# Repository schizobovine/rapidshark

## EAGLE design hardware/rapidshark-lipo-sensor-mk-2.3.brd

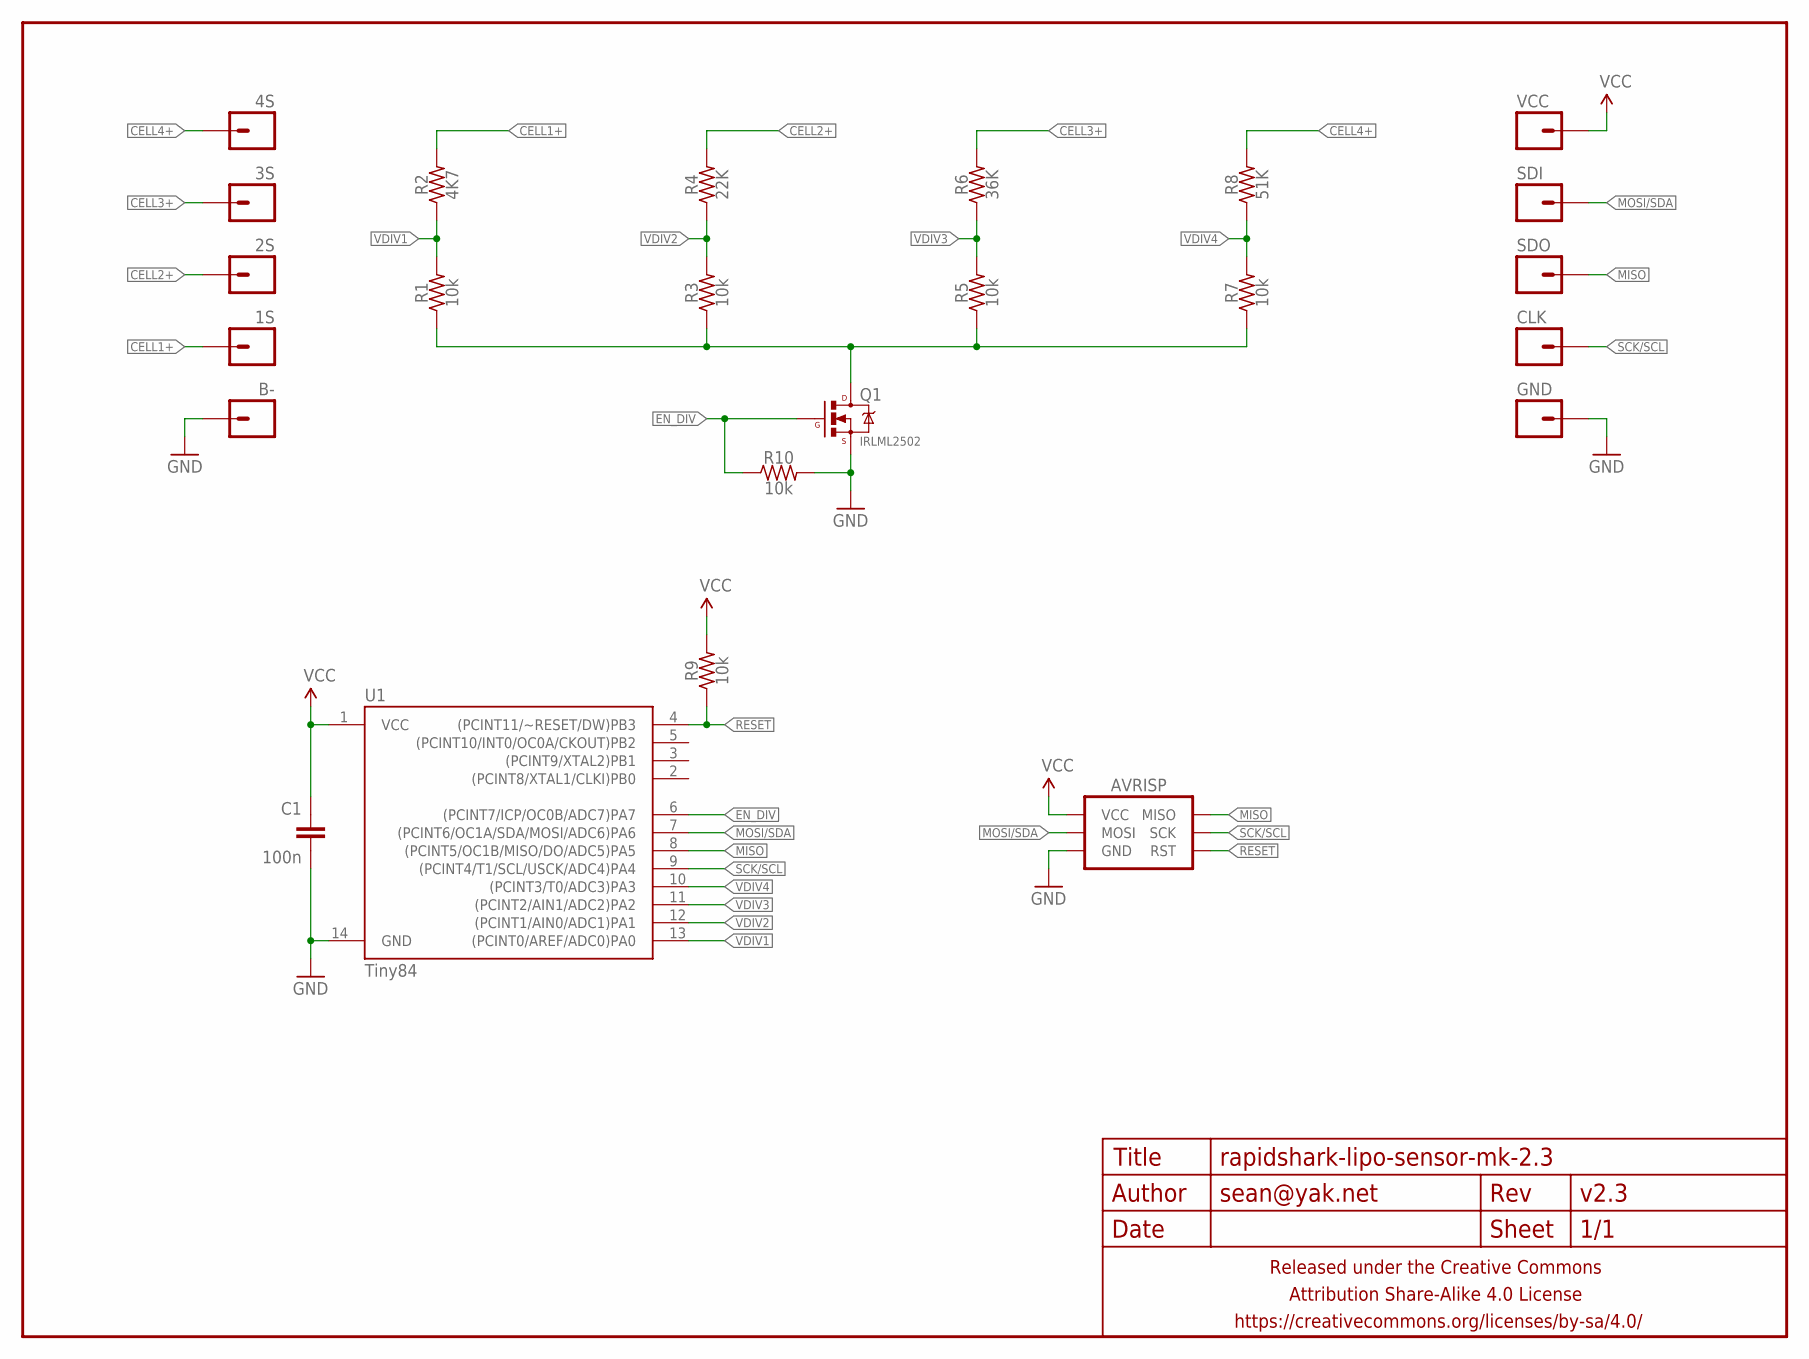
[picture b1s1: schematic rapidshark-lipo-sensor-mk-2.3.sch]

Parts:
1S, 2S, 3S, 4S: M01PTH-0.9MM; 1X01-0.9MM
AVRISP: AVR_SPI_PRG_6TESTPOINTS; 2X3_TEST_POINTS
B-: M01PTH-0.9MM; 1X01-0.9MM
C1: 100n; C0603-TIGHTER
CLK: M01PTH-0.9MM; 1X01-0.9MM
FRAME1: FRAME-LETTERNO_PACKAGE; DUMMY
GND: M01PTH-0.9MM; 1X01-0.9MM
Q1: IRLML2502; SOT23
R1, R3, R5, R7, R9, R10: 10k; R0603-TIGHTER
R2: 4K7; R0603-TIGHTER
R4: 22K; R0603-TIGHTER
R6: 36K; R0603-TIGHTER
R8: 51K; R0603-TIGHTER
SDI: M01PTH-0.9MM; 1X01-0.9MM
SDO: M01PTH-0.9MM; 1X01-0.9MM
U1: Tiny84; SO14
VCC: M01PTH-0.9MM; 1X01-0.9MM

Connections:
CELL1+: 1S.1, R2.2
CELL2+: 2S.1, R4.2
CELL3+: 3S.1, R6.2
CELL4+: 4S.1, R8.2
EN_DIV: Q1.1 (G), R10.1, U1.6 ((PCINT7/ICP/OC0B/ADC7)PA7)
GND: AVRISP.6 (GND), B-.1, C1.2, GND.1, Q1.2 (S), R10.2, U1.14 (GND)
MISO: AVRISP.1 (MISO), SDO.1, U1.8 ((PCINT5/OC1B/MISO/DO/ADC5)PA5)
MOSI/SDA: AVRISP.4 (MOSI), SDI.1, U1.7 ((PCINT6/OC1A/SDA/MOSI/ADC6)PA6)
unnamed: Q1.3 (D), R1.1, R3.1, R5.1, R7.1
RESET: AVRISP.5 (RST), R9.1, U1.4 ((PCINT11/~RESET/DW)PB3)
SCK/SCL: AVRISP.3 (SCK), CLK.1, U1.9 ((PCINT4/T1/SCL/USCK/ADC4)PA4)
VCC: AVRISP.2 (VCC), C1.1, R9.2, U1.1 (VCC), VCC.1
VDIV1: R1.2, R2.1, U1.13 ((PCINT0/AREF/ADC0)PA0)
VDIV2: R3.2, R4.1, U1.12 ((PCINT1/AIN0/ADC1)PA1)
VDIV3: R5.2, R6.1, U1.11 ((PCINT2/AIN1/ADC2)PA2)
VDIV4: R7.2, R8.1, U1.10 ((PCINT3/T0/ADC3)PA3)

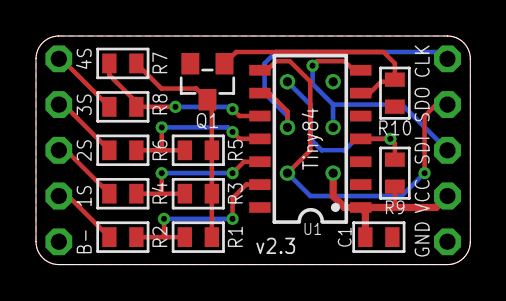
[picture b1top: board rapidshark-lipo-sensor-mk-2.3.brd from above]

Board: 2 copper layers, 24.1 x 12.7 mm, 25 parts (1 on the bottom side), 16 nets.

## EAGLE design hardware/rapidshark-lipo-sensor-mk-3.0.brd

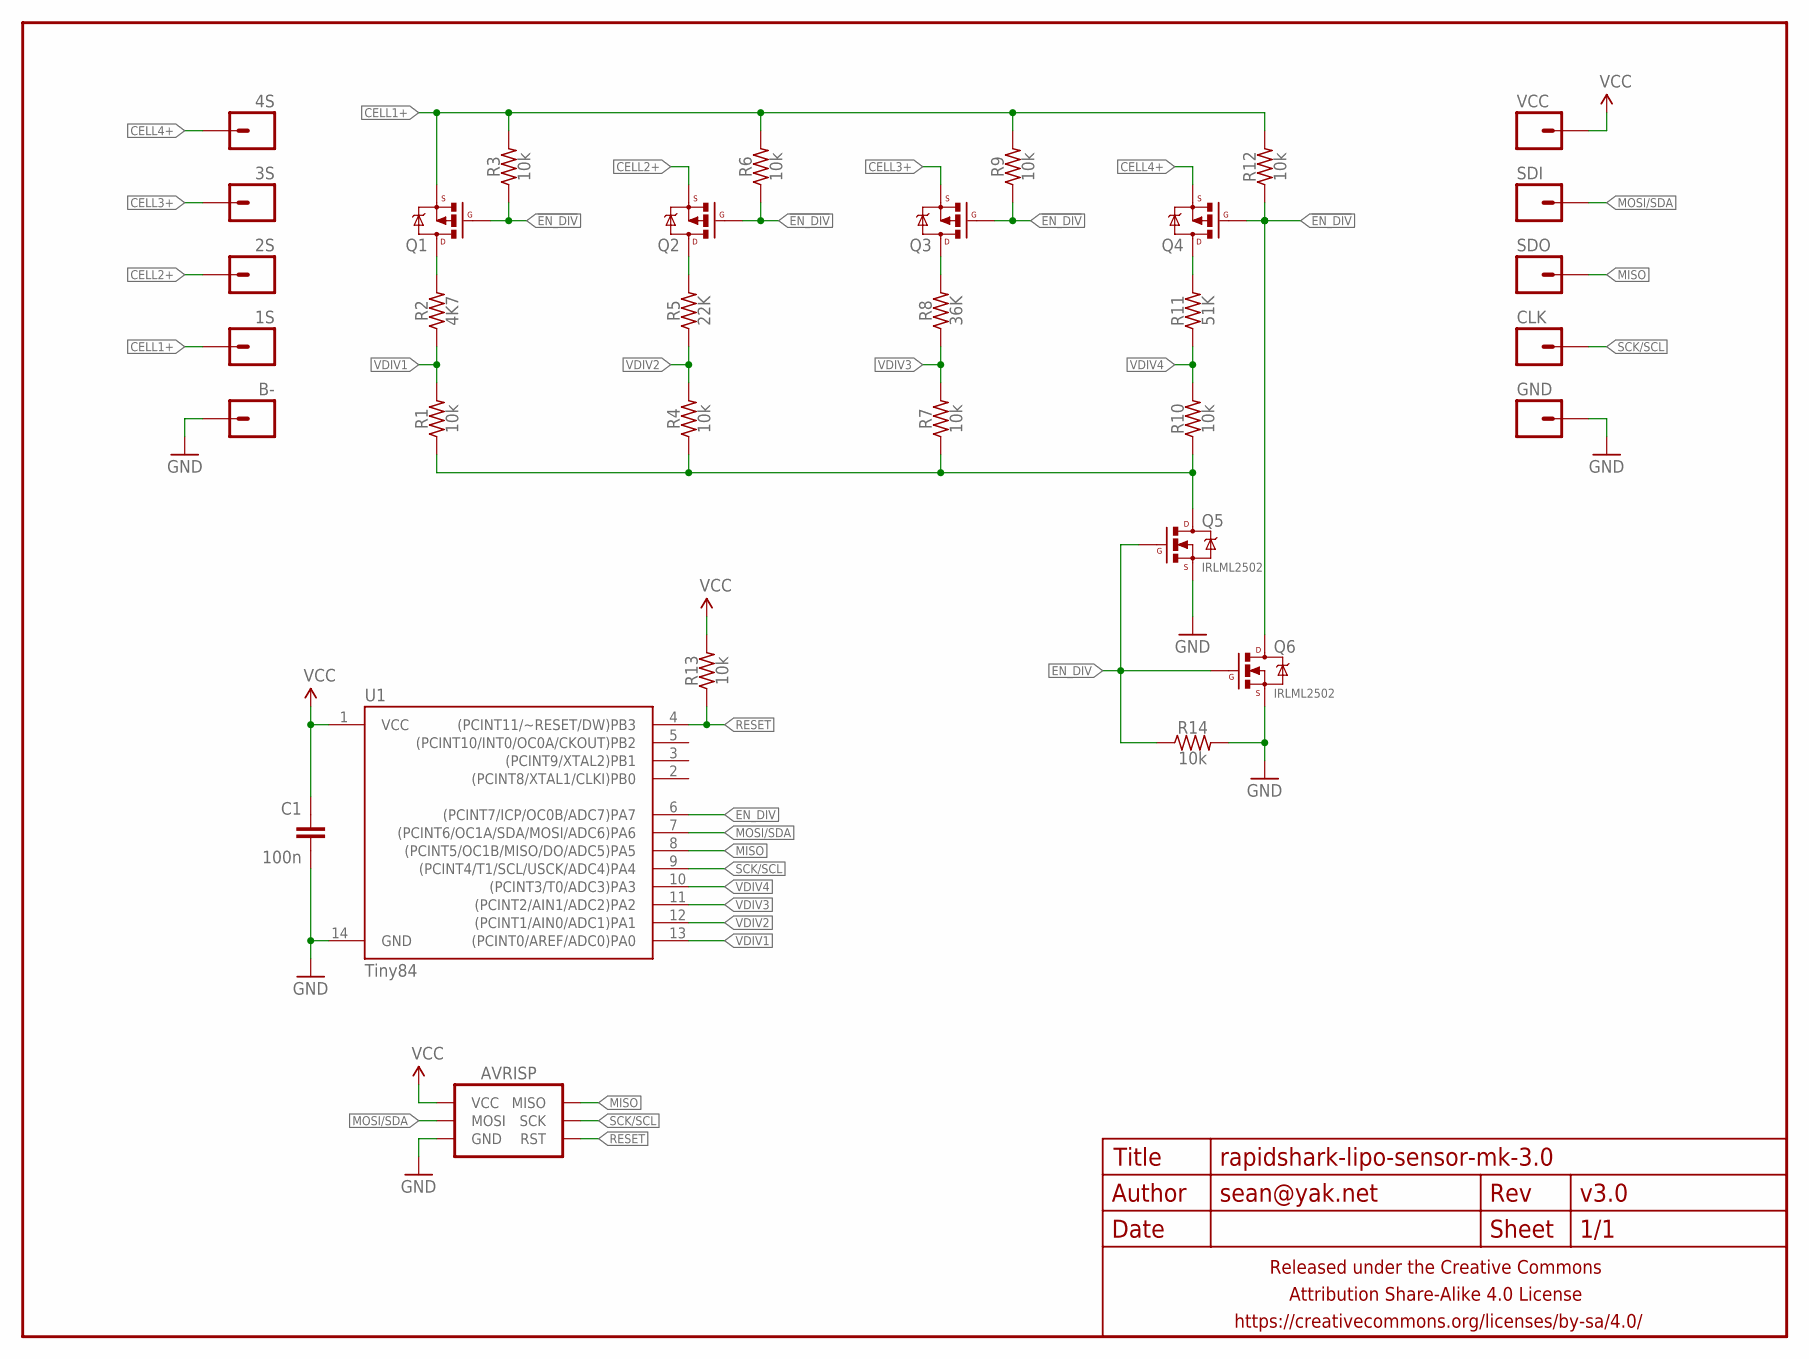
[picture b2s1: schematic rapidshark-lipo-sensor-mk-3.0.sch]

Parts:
1S, 2S, 3S, 4S: M01PTH-0.9MM; 1X01-0.9MM
AVRISP: AVR_SPI_PRG_6SMD_TEST_POINTS; 2X3_SMD_TEST_POINTS
B-: M01PTH-0.9MM; 1X01-0.9MM
C1: 100n; C0603-TIGHTER
CLK: M01PTH-0.9MM; 1X01-0.9MM
FRAME1: FRAME-LETTERNO_PACKAGE; DUMMY
GND: M01PTH-0.9MM; 1X01-0.9MM
Q1, Q2, Q3, Q4: MOSFET-PCHANNELSOT-23; SOT23
Q5, Q6: IRLML2502; SOT23
R1, R3, R4, R6, R7, R9, R10, R12, R13, R14: 10k; R0603-TIGHTER
R2: 4K7; R0603-TIGHTER
R5: 22K; R0603-TIGHTER
R8: 36K; R0603-TIGHTER
R11: 51K; R0603-TIGHTER
SDI: M01PTH-0.9MM; 1X01-0.9MM
SDO: M01PTH-0.9MM; 1X01-0.9MM
U1: Tiny84; SO14
VCC: M01PTH-0.9MM; 1X01-0.9MM

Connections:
!EN_DIV: Q1.1 (G), Q2.1 (G), Q3.1 (G), Q4.1 (G), Q6.3 (D), R3.1, R6.1, R9.1, R12.1
CELL1+: 1S.1, Q1.2 (S), R3.2, R6.2, R9.2, R12.2
CELL2+: 2S.1, Q2.2 (S)
CELL3+: 3S.1, Q3.2 (S)
CELL4+: 4S.1, Q4.2 (S)
EN_DIV: Q5.1 (G), Q6.1 (G), R14.1, U1.6 ((PCINT7/ICP/OC0B/ADC7)PA7)
GND: AVRISP.6 (GND), B-.1, C1.2, GND.1, Q5.2 (S), Q6.2 (S), R14.2, U1.14 (GND)
MISO: AVRISP.1 (MISO), SDO.1, U1.8 ((PCINT5/OC1B/MISO/DO/ADC5)PA5)
MOSI/SDA: AVRISP.4 (MOSI), SDI.1, U1.7 ((PCINT6/OC1A/SDA/MOSI/ADC6)PA6)
unnamed: Q5.3 (D), R1.1, R4.1, R7.1, R10.1
unnamed: Q2.3 (D), R5.2
unnamed: Q3.3 (D), R8.2
unnamed: Q4.3 (D), R11.2
unnamed: Q1.3 (D), R2.2
RESET: AVRISP.5 (RST), R13.1, U1.4 ((PCINT11/~RESET/DW)PB3)
SCK/SCL: AVRISP.3 (SCK), CLK.1, U1.9 ((PCINT4/T1/SCL/USCK/ADC4)PA4)
VCC: AVRISP.2 (VCC), C1.1, R13.2, U1.1 (VCC), VCC.1
VDIV1: R1.2, R2.1, U1.13 ((PCINT0/AREF/ADC0)PA0)
VDIV2: R4.2, R5.1, U1.12 ((PCINT1/AIN0/ADC1)PA1)
VDIV3: R7.2, R8.1, U1.11 ((PCINT2/AIN1/ADC2)PA2)
VDIV4: R10.2, R11.1, U1.10 ((PCINT3/T0/ADC3)PA3)

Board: 2 copper layers, 34 parts (1 on the bottom side), 21 nets, no tracks yet.

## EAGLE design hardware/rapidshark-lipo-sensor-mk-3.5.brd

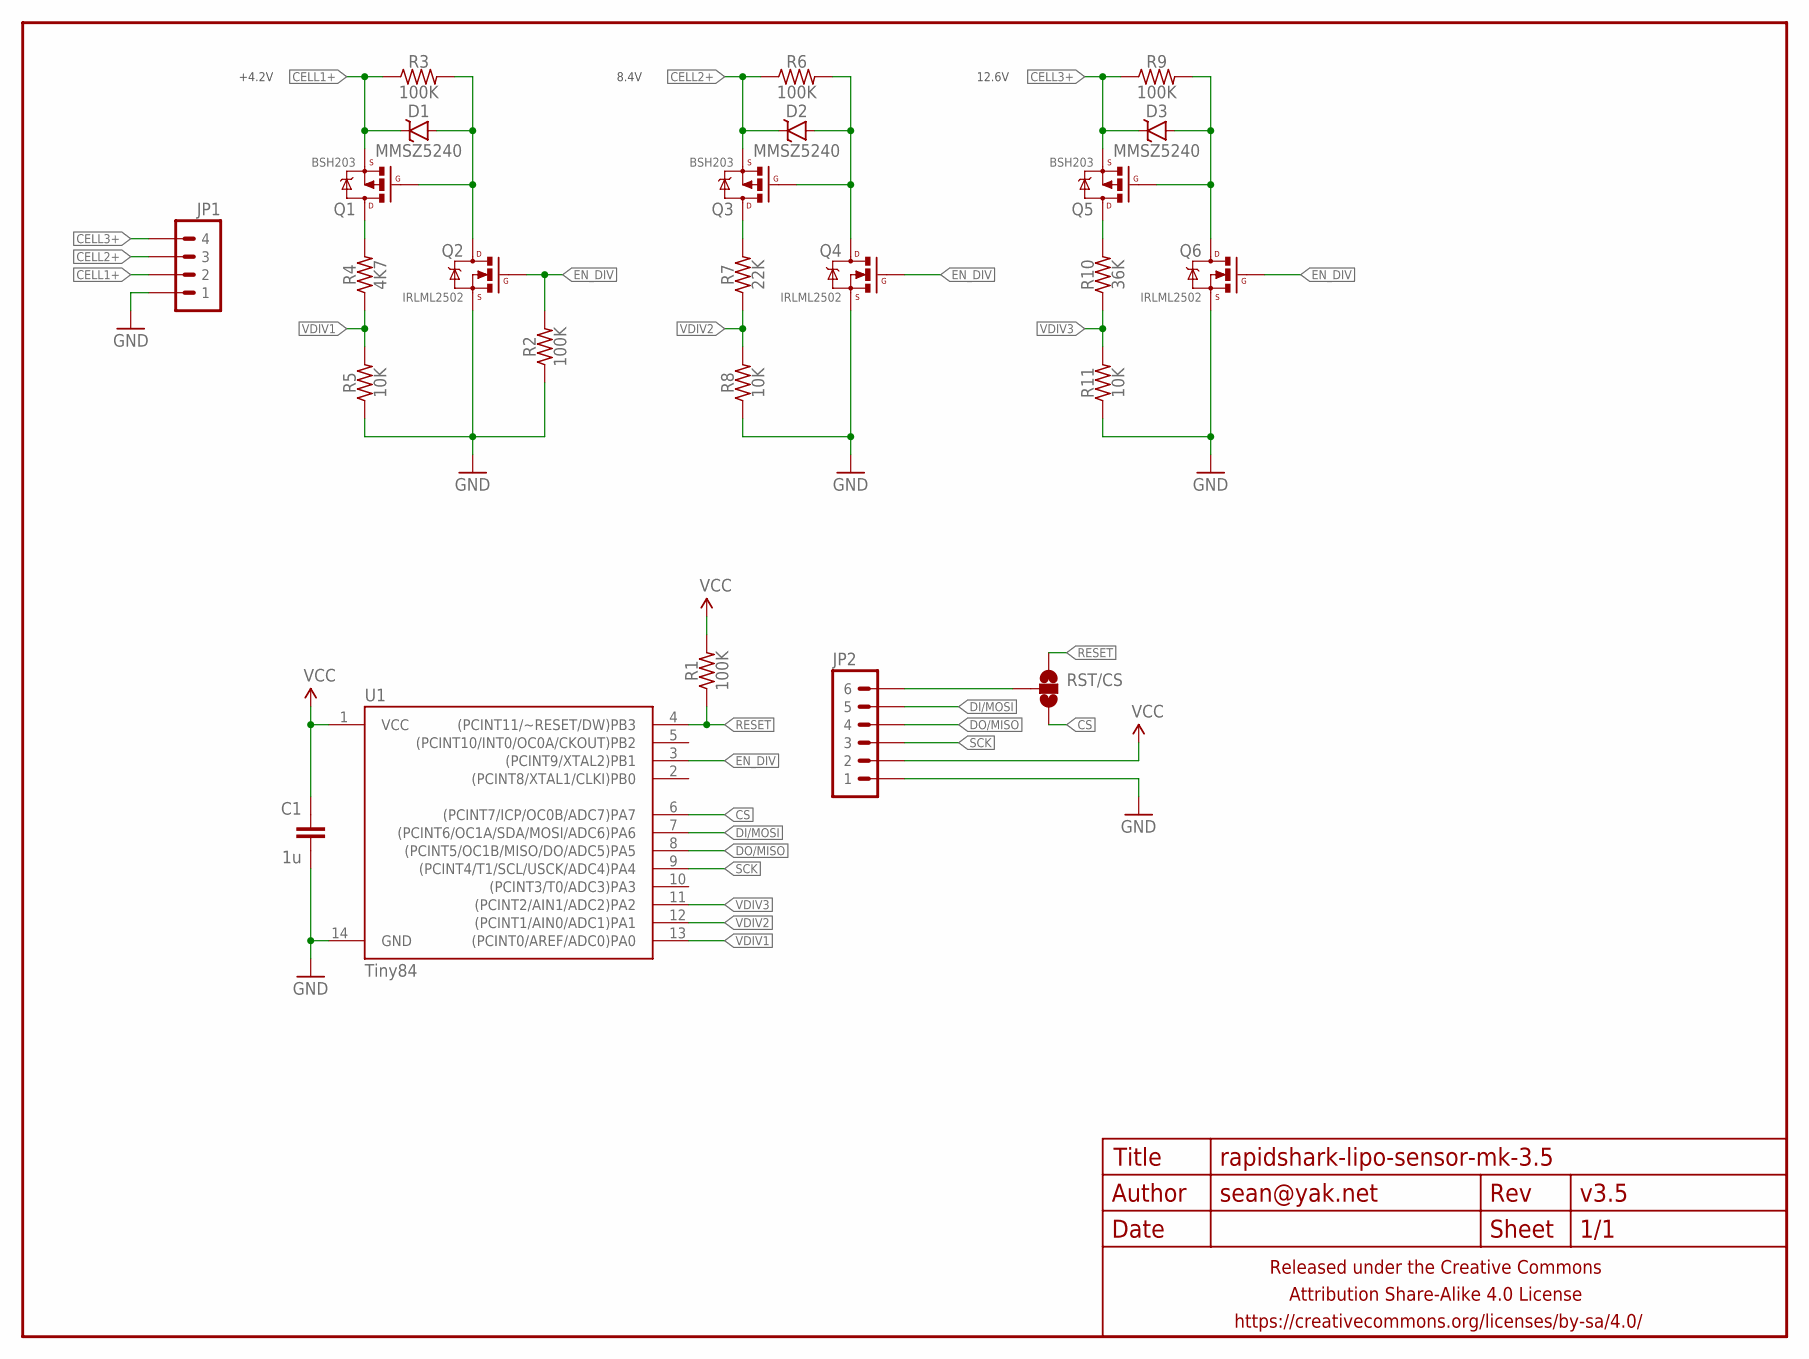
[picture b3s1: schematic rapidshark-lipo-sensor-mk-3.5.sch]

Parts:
C1: 1u; C0603-TIGHTER
D1, D2, D3: MMSZ5240; SOD323-ZENNER
FRAME1: FRAME-LETTERNO_PACKAGE; DUMMY
JP1: M04JST_XH_RA; JST-4-XH-RA-PTH
JP2: M06PTH_CENTERED; 1X06_CENTERED
Q1, Q3, Q5: BSH203; SOT23
Q2, Q4, Q6: IRLML2502; SOT23
R1, R2, R3, R6, R9: 100K; R0603-TIGHTER
R4: 4K7; R0603-TIGHTER
R5, R8, R11: 10K; R0603-TIGHTER
R7: 22K; R0603-TIGHTER
R10: 36K; R0603-TIGHTER
RST/CS: JUMPER-PAD-3-NOFULL_BOX_SILK; PAD-JUMPER-3-NO_YES_SILK_FULL_BOX
U1: Tiny84; SO14

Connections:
CELL1+: D1.C, JP1.2, Q1.2 (S), R3.1
CELL2+: D2.C, JP1.3, Q3.2 (S), R6.1
CELL3+: D3.C, JP1.4, Q5.2 (S), R9.1
CS: RST/CS.3, U1.6 ((PCINT7/ICP/OC0B/ADC7)PA7)
DI/MOSI: JP2.5, U1.7 ((PCINT6/OC1A/SDA/MOSI/ADC6)PA6)
DO/MISO: JP2.4, U1.8 ((PCINT5/OC1B/MISO/DO/ADC5)PA5)
EN_DIV: Q2.1 (G), Q4.1 (G), Q6.1 (G), R2.2, U1.3 ((PCINT9/XTAL2)PB1)
GND: C1.2, JP1.1, JP2.1, Q2.2 (S), Q4.2 (S), Q6.2 (S), R2.1, R5.1, R8.1, R11.1, U1.14 (GND)
unnamed: Q3.3 (D), R7.2
unnamed: Q5.3 (D), R10.2
unnamed: D1.A, Q1.1 (G), Q2.3 (D), R3.2
unnamed: D2.A, Q3.1 (G), Q4.3 (D), R6.2
unnamed: Q1.3 (D), R4.2
unnamed: D3.A, Q5.1 (G), Q6.3 (D), R9.2
RESET: R1.1, RST/CS.1, U1.4 ((PCINT11/~RESET/DW)PB3)
RST/CS: JP2.6, RST/CS.2
SCK: JP2.3, U1.9 ((PCINT4/T1/SCL/USCK/ADC4)PA4)
VCC: C1.1, JP2.2, R1.2, U1.1 (VCC)
VDIV1: R4.1, R5.2, U1.13 ((PCINT0/AREF/ADC0)PA0)
VDIV2: R7.1, R8.2, U1.12 ((PCINT1/AIN0/ADC1)PA1)
VDIV3: R10.1, R11.2, U1.11 ((PCINT2/AIN1/ADC2)PA2)

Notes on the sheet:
+4.2V
8.4V
12.6V

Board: 2 copper layers, 26 parts (0 on the bottom side), 21 nets, no tracks yet.

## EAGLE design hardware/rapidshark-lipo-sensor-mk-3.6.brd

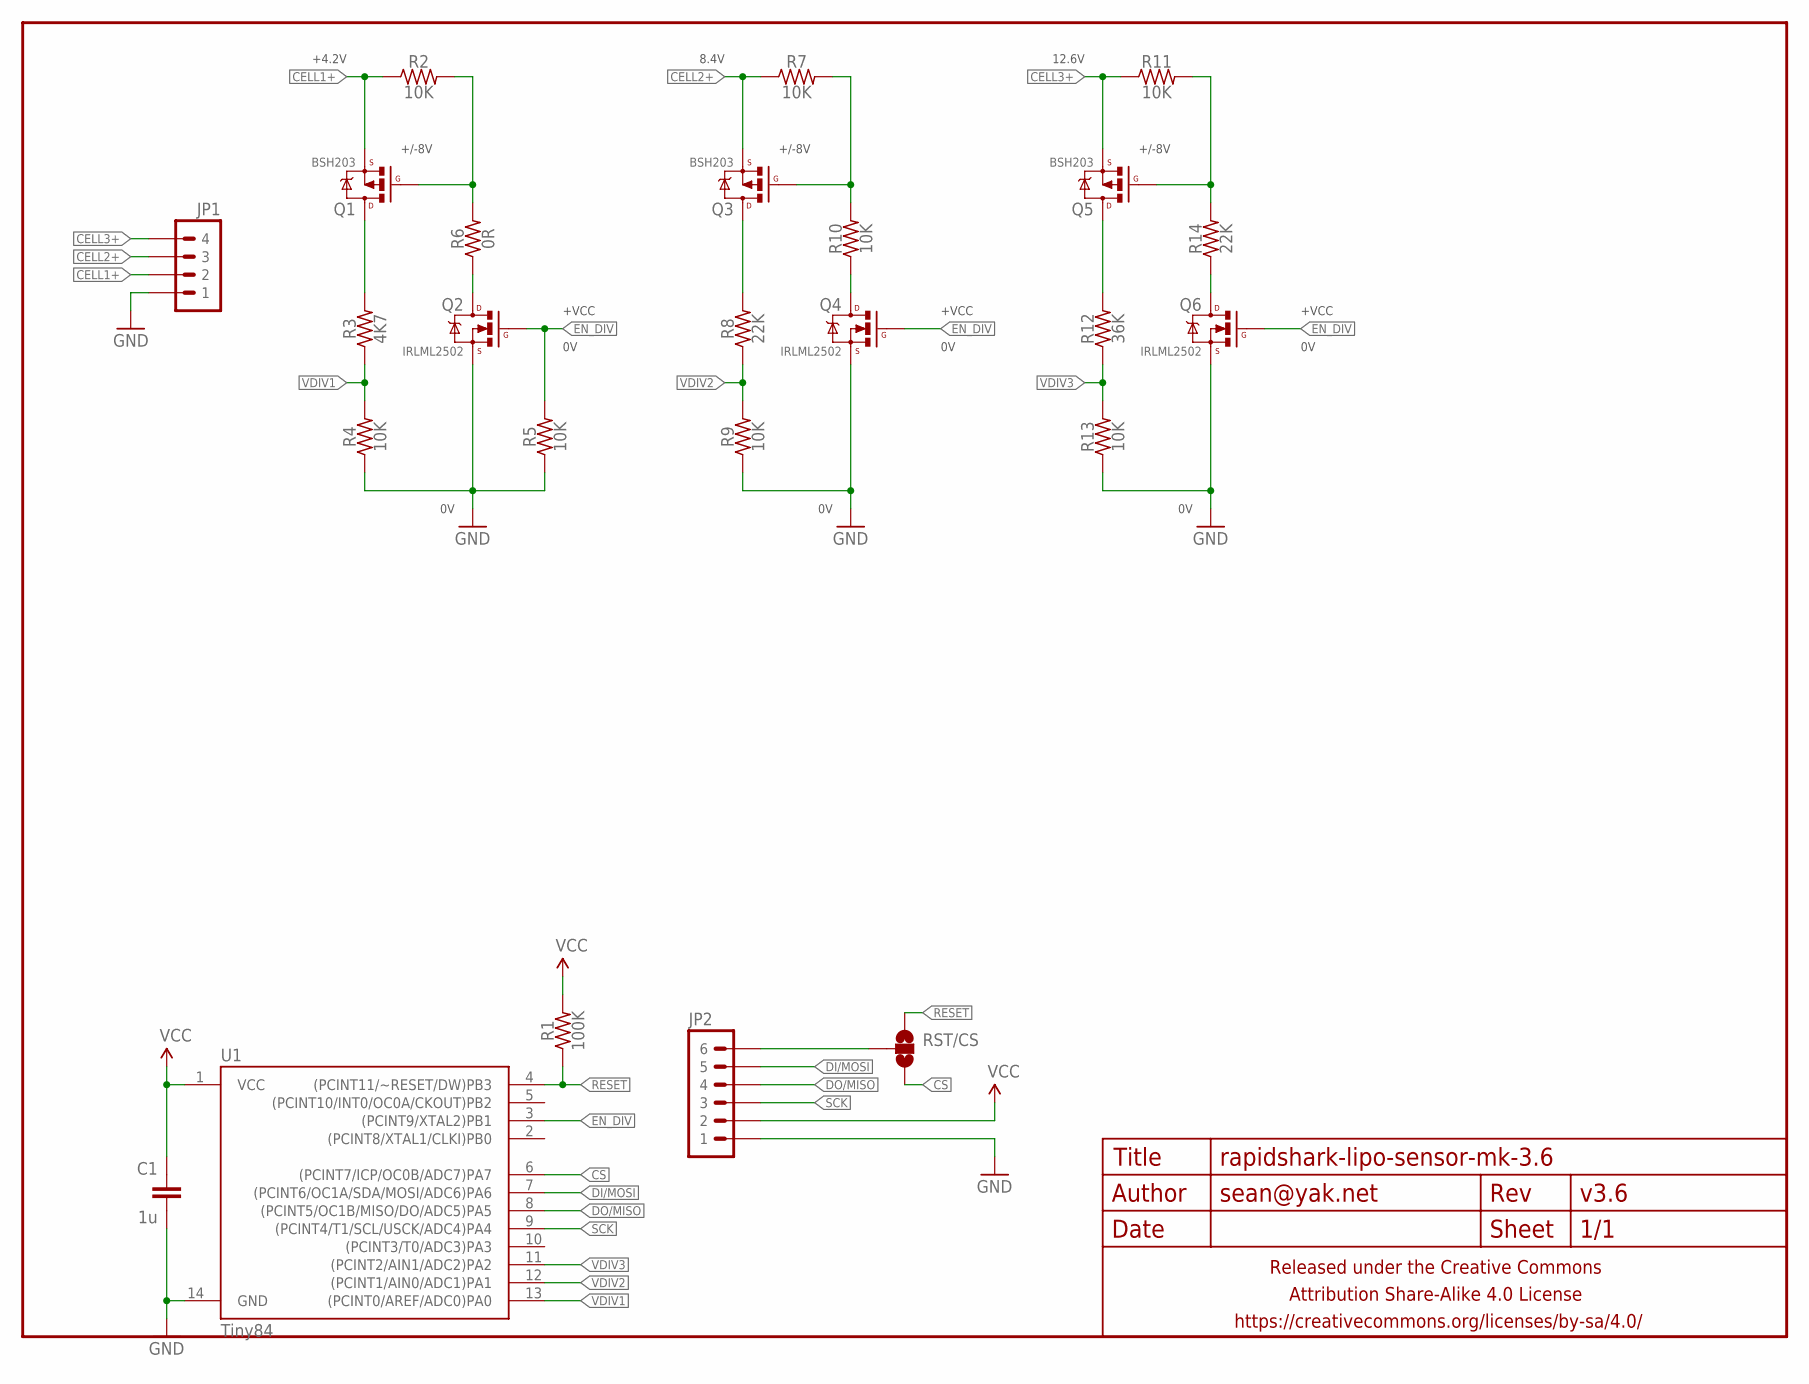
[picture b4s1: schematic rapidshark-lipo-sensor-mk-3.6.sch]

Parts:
C1: 1u; C0603-TIGHTER
FRAME1: FRAME-LETTERNO_PACKAGE; DUMMY
JP1: M04JST_XH_RA; JST-4-XH-RA-PTH
JP2: M06PTH_CENTERED; 1X06_CENTERED
Q1, Q3, Q5: BSH203; SOT23
Q2, Q4, Q6: IRLML2502; SOT23
R1: 100K; R0603-TIGHTER
R2, R4, R5, R7, R9, R10, R11, R13: 10K; R0603-TIGHTER
R3: 4K7; R0603-TIGHTER
R6: 0R; R0603-TIGHTER
R8, R14: 22K; R0603-TIGHTER
R12: 36K; R0603-TIGHTER
RST/CS: JUMPER-PAD-3-NOFULL_BOX_SILK; PAD-JUMPER-3-NO_YES_SILK_FULL_BOX
U1: Tiny84; SO14

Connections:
CELL1+: JP1.2, Q1.2 (S), R2.1
CELL2+: JP1.3, Q3.2 (S), R7.1
CELL3+: JP1.4, Q5.2 (S), R11.1
CS: RST/CS.3, U1.6 ((PCINT7/ICP/OC0B/ADC7)PA7)
DI/MOSI: JP2.5, U1.7 ((PCINT6/OC1A/SDA/MOSI/ADC6)PA6)
DO/MISO: JP2.4, U1.8 ((PCINT5/OC1B/MISO/DO/ADC5)PA5)
EN_DIV: Q2.1 (G), Q4.1 (G), Q6.1 (G), R5.2, U1.3 ((PCINT9/XTAL2)PB1)
GND: C1.2, JP1.1, JP2.1, Q2.2 (S), Q4.2 (S), Q6.2 (S), R4.1, R5.1, R9.1, R13.1, U1.14 (GND)
unnamed: Q4.3 (D), R10.1
unnamed: Q3.3 (D), R8.2
unnamed: Q5.3 (D), R12.2
unnamed: Q1.1 (G), R2.2, R6.2
unnamed: Q3.1 (G), R7.2, R10.2
unnamed: Q1.3 (D), R3.2
unnamed: Q5.1 (G), R11.2, R14.2
unnamed: Q6.3 (D), R14.1
unnamed: Q2.3 (D), R6.1
RESET: R1.1, RST/CS.1, U1.4 ((PCINT11/~RESET/DW)PB3)
RST/CS: JP2.6, RST/CS.2
SCK: JP2.3, U1.9 ((PCINT4/T1/SCL/USCK/ADC4)PA4)
VCC: C1.1, JP2.2, R1.2, U1.1 (VCC)
VDIV1: R3.1, R4.2, U1.13 ((PCINT0/AREF/ADC0)PA0)
VDIV2: R8.1, R9.2, U1.12 ((PCINT1/AIN0/ADC1)PA1)
VDIV3: R12.1, R13.2, U1.11 ((PCINT2/AIN1/ADC2)PA2)

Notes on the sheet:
+4.2V
8.4V
12.6V
+VCC
+/-8V

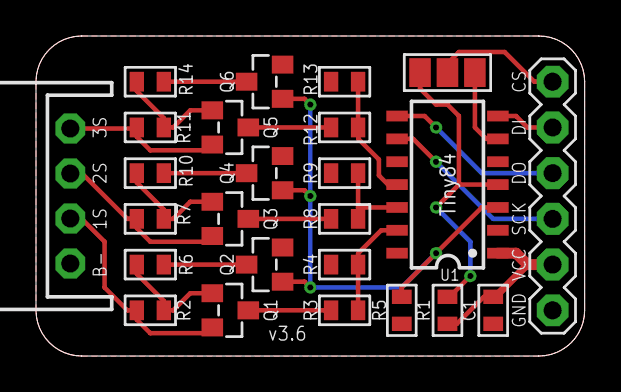
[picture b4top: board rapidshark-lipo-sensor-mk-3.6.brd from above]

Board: 2 copper layers, 30.5 x 17.8 mm, 26 parts (0 on the bottom side), 24 nets.

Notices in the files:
hardware/rapidshark-lipo-sensor-mk-3.5.brd:
CC-BY-SA-4.0
parts and their libraries:
A_butts: Released under the Creative Commons Attribution Share-Alike 4.0 License
A_butts: https://creativecommons.org/licenses/by-sa/4.0
A_butts: Released under the Creative Commons
